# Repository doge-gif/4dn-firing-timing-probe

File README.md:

# 4dn-firing-timing-probe

A Raspberry Pi Pico (RP2040) bench instrument that maps the ignition **advance
curve (°BTDC vs RPM)** of a Denso TNDF17 TCI ignitor (as fitted to the Yamaha
SRV250, renessa). It emulates the crankshaft pickup at a commanded RPM,
timestamps the resulting ignition-coil fire events, and writes the per-cylinder
timing to CSV files on an onboard FAT volume, retrieved over USB mass storage.

No engine required: the Pico is both the stimulus (a synthesized pickup pattern)
and the instrument (dual-edge capture + crank-angle reconstruction).

> [!NOTE]
> This project is created with the help of AI. The schematic is made manually,
> but the firmware and documentation are generated with claude code.

## How it works

The Pico drives a synthesized VR/pickup pulse train on GP18 matching the SRV250
trigger wheel (4 teeth, 60/60/60/180°) at a commanded RPM. It captures both
edges of the ignitor's two coil outputs (GP16/GP17) and of its own emitted
pickup (GP18 self-capture) with the PIO on one shared 62.5 MHz timebase, then
computes each spark's °BTDC by interpolating its position between the bracketing
pickup edges relative to per-cylinder TDC. Details in
[docs/architecture.md](docs/architecture.md).

## Run modes & output

`RUN_MODE` in `CONFIG.INI` selects the run; results land as CSV on the USB drive:

| Mode | What it does | Output |
|------|--------------|--------|
| `STEPPED` | Hold each RPM step, average N samples → advance map | `MAP_###.CSV` |
| `RAMP_UP` / `RAMP_DOWN` | Continuous RPM sweep, one row per spark | `RAMPU###.CSV` / `RAMPD###.CSV` |
| `HOLD` | Hold a constant RPM indefinitely, one row per spark | `HOLD###.CSV` |

## Quick start

1. **Flash the firmware.** Download the latest
   prober.uf2 from the project's GitHub [Releases][] page, then hold
   **BOOTSEL** while plugging in the Pico (it mounts as `RPI-RP2`) and copy the
   `.uf2` onto it. (Building from source instead:
   [docs/development.md](docs/development.md).)
2. **Wire the harness** to the ignitor — pin map in
   [docs/architecture.md](docs/architecture.md#hardware); board files and
   PCB/breadboard notes in [schematics/](schematics/README.md).
3. Mount the Pico's USB drive and edit `CONFIG.INI` — **run parameters only**;
   the wheel/TDC geometry is baked into the firmware.
4. **Reset** the Pico (config is read at boot), wait for the LED at 1 Hz
   (Ready), then press **BOOTSEL** to start the run.
5. Wait for the LED to return to steady **1 Hz (Ready)** — the run finished and
   the CSV is flushed — then replug the drive and copy the file. (Copying before
   the LED is Ready is too early; the file is written only at end-of-run.)

[Releases]: https://github.com/doge-gif/4dn-firing-timing-probe/releases/latest

## Repository layout

```
firmware/      C++20 firmware — core/ (SDK-free, host-tested), hal/, app/, tests/
schematics/    KiCad board + PCB/breadboard notes (schematics/README.md)
ci/            CI entry point (container build + lint + test)
docs/          architecture.md, development.md, refs/ (third-party sources)
results/       CSV output from my runs
flake.nix      Nix devShell (pinned toolchain: arm-none-eabi-gcc, probe-rs, …)
```

## License

Project source: see [LICENSE](LICENSE). Third-party reference materials indexed
in [docs/refs/SOURCES.md](docs/refs/SOURCES.md) remain under their own licenses.

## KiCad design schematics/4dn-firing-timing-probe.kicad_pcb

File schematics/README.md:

# 4DN Firing Timing Probe Schematics

This directory contains the schematics for the 4DN Firing Timing Probe.
See [releases][]: schematic.pdf for a PDF version.

The probe is simple enough that it'll work with a breadboard or protoboard. If
you want a proper PCB, use KiCad (10+) and send the gerbers to a fab house.

A gerber file for jlcpcb can be found in [releases][]: 4dn-firing-timing-probe-gerbers.zip.

[releases]: https://github.com/doge-gif/4dn-firing-timing-probe/releases/latest

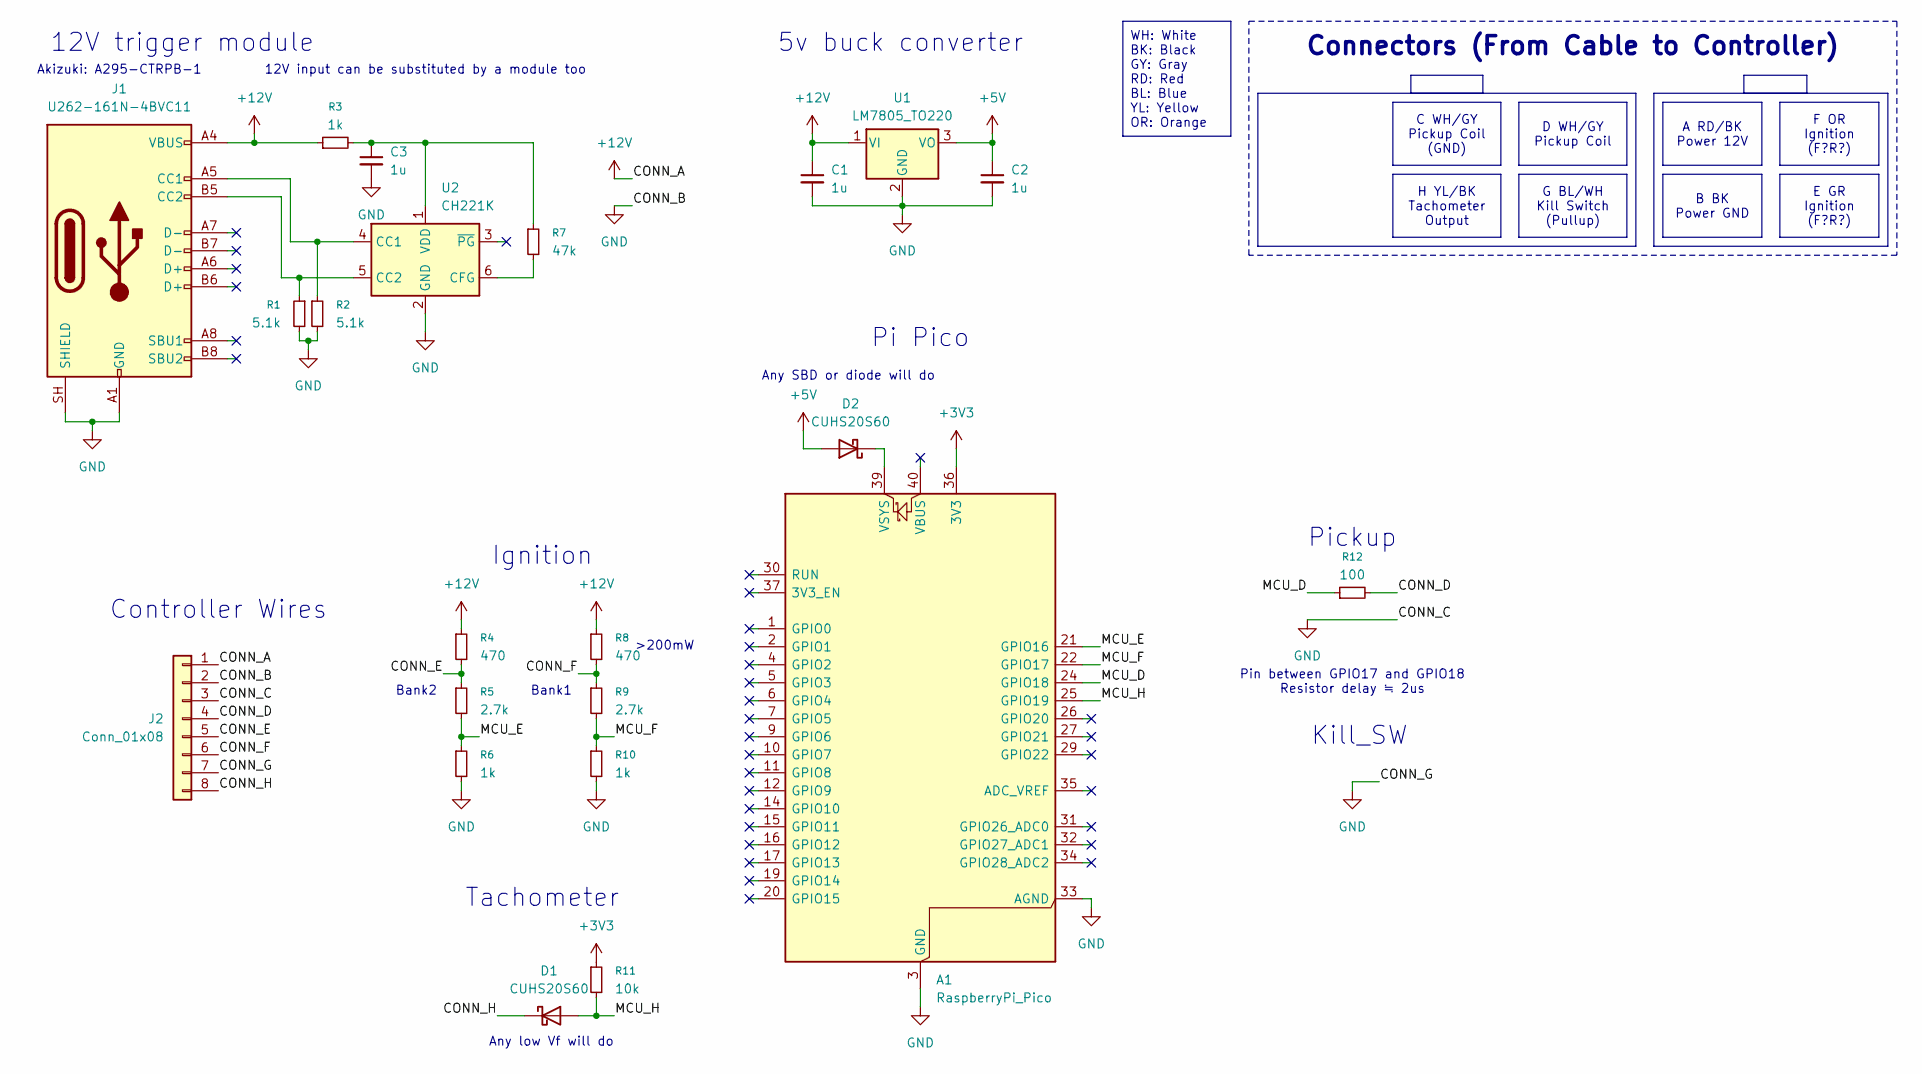
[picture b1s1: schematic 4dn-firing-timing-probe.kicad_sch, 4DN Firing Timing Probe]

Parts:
A1: RaspberryPi_Pico; RaspberryPi_Pico_Common_SMD
C1, C2, C3: 1u; C_0603_1608Metric
D1, D2: CUHS20S60; D_TUMD2
J1: U262-161N-4BVC11; USB_C_Receptacle_Palconn_UTC16-G
J2: Conn_01x08; PinHeader_1x08_P2.54mm_Vertical
R1, R2: 5.1k; R_0603_1608Metric
R3, R6, R10: 1k; R_0603_1608Metric
R4, R8: 470; R_1206_3216Metric
R5, R9: 2.7k; R_0603_1608Metric
R7: 47k; R_0603_1608Metric
R11: 10k; R_0603_1608Metric
R12: 100; R_0603_1608Metric
U1: LM7805_TO220; TO-220-3_Vertical
U2: CH221K; SOT-23-6

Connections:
+3V3: A1.36 (3V3), R11.1
+5V: C2.1, D2.2 (A), U1.3 (VO)
+12V: C1.1, J1.A4 (VBUS), J1.A9 (VBUS), J1.B4 (VBUS), J1.B9 (VBUS), J2.1, R3.1, R4.1, R8.1, U1.1 (VI)
/CONN_D: J2.4, R12.2
/CONN_E: J2.5, R4.2, R5.1
/CONN_F: J2.6, R8.2, R9.1
/CONN_H: D1.1 (K), J2.8
/MCU_D: A1.24 (GPIO18), R12.1
/MCU_E: A1.21 (GPIO16), R5.2, R6.1
/MCU_F: A1.22 (GPIO17), R9.2, R10.1
/MCU_H: A1.25 (GPIO19), D1.2 (A), R11.2
GND: A1.3 (GND), A1.8 (GND), A1.13 (GND), A1.18 (GND), A1.23 (GND), A1.28 (GND), A1.33 (AGND), A1.38 (GND), C1.2, C2.2, C3.2, J1.A1 (GND), J1.A12 (GND), J1.B1 (GND), J1.B12 (GND), J1.SH (SHIELD), J2.2, J2.3, J2.7, R1.2, R2.2, R6.2, R10.2, U1.2 (GND), U2.2 (GND)
unnamed: A1.39 (VSYS), D2.1 (K)
unnamed: J1.A5 (CC1), R2.1, U2.4 (CC1)
unnamed: J1.B5 (CC2), R1.1, U2.5 (CC2)
unnamed: R7.2, U2.6 (CFG)
unnamed: C3.1, R3.2, R7.1, U2.1 (VDD)

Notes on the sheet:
Bank2
Ignition
Tachometer
Akizuki: A295-CTRPB-1
Controller Wires
Pi Pico
Any low Vf will do
Any SBD or diode will do
Pickup
5v buck converter
Kill_SW
>200mW
Bank1
12V input can be substituted by a module too
12V trigger module
Pin between GPIO17 and GPIO18 Resistor delay ≒ 2us
A RD/BK Power 12V
G BL/WH Kill Switch (Pullup)
C WH/GY Pickup Coil (GND)
E GR Ignition (F?R?)
Connectors (From Cable to Controller)
B BK Power GND
D WH/GY Pickup Coil
WH: White BK: Black GY: Gray RD: Red BL: Blue YL: Yellow OR: Orange
F OR Ignition (F?R?)
H YL/BK Tachometer Output

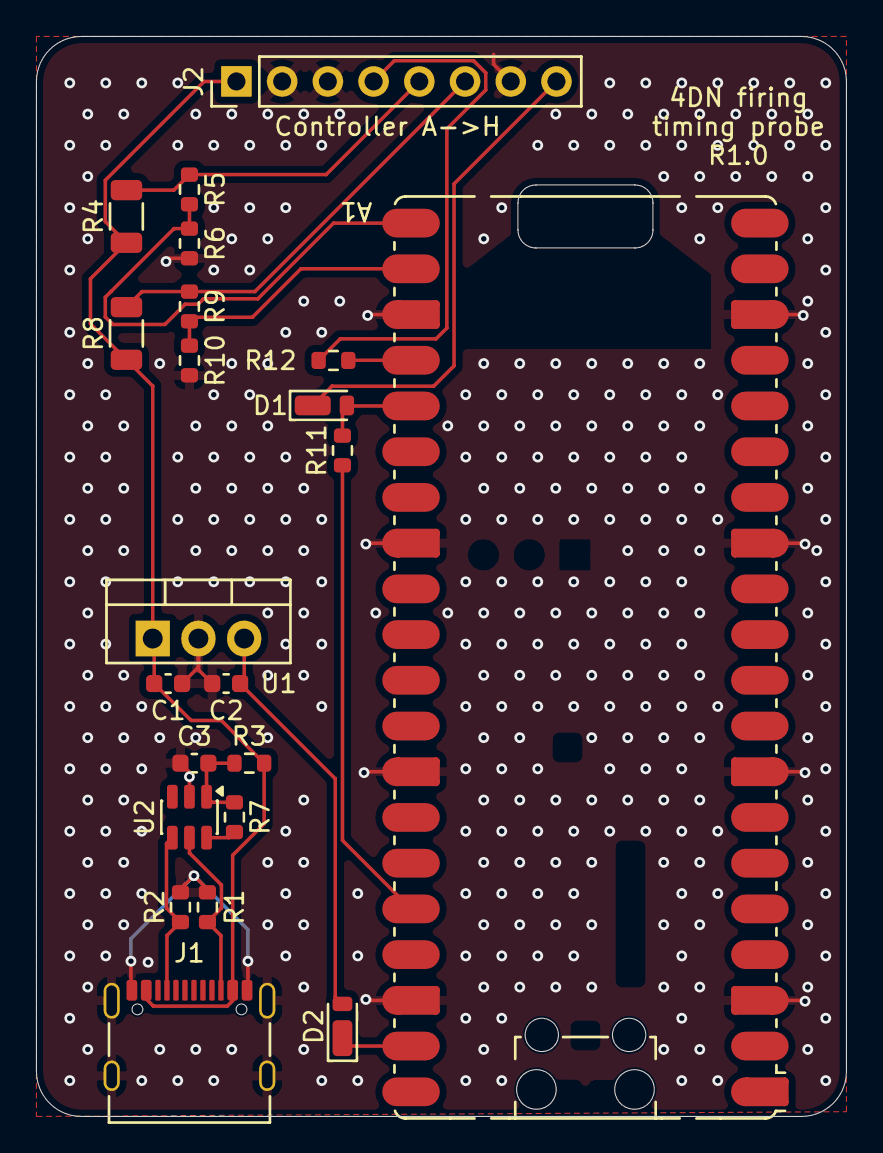
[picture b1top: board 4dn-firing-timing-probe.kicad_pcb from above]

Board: 2 copper layers, 45.0 x 60.0 mm, 22 parts (0 on the bottom side), 17 nets.
